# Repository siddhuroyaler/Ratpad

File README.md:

# Ratpad
It is my Hack club's project Hackpad 

I named my Hackpad Ratpad( i dont know why name it that just poped in my mind) 

# Challenges:-

It is my 1 st Hackclub projet , it was hard and confusing most of the confusion is in firmware and most of the time consuming was 3D model as it was my 1 my time makeing a 3D model 

# Specifications:-

 BOM:

5x Cherry MX Switches

6x SK6812 MINI Leds

1x XIAO RP2040

1x EC11 Rotary encoders

1x 0.91 inch OLED displays 

5x Blank DSA Keycaps

4x M3x16 Bolt

4x M3 Heatset

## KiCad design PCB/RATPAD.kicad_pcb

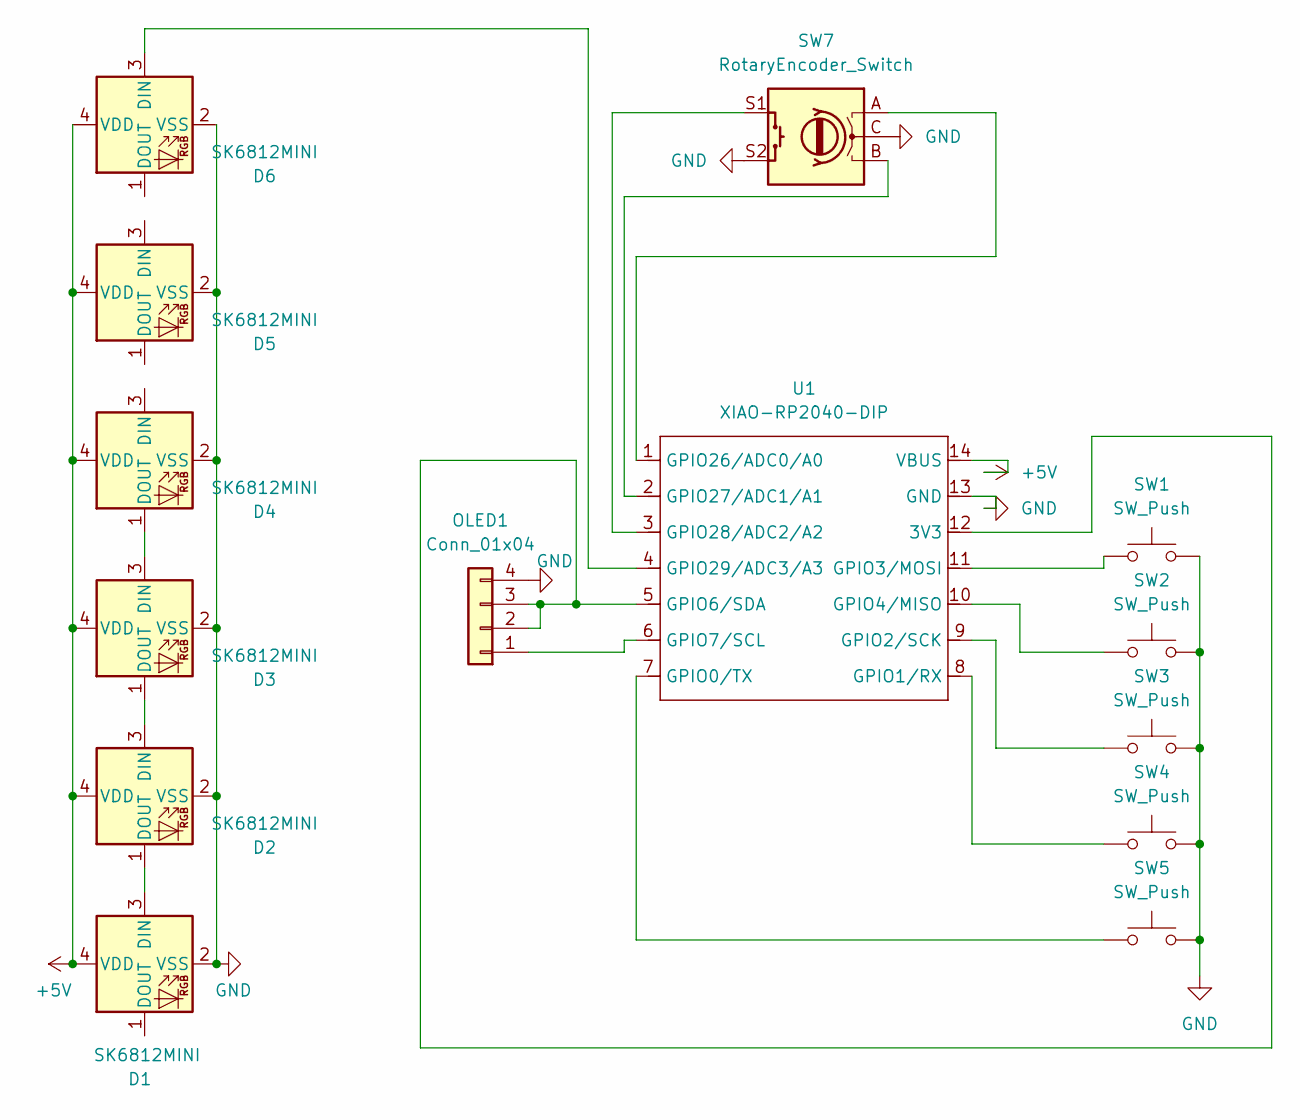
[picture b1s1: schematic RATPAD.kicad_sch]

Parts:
D1, D2, D3, D4, D5, D6: SK6812MINI; MX_SK6812MINI-E_REV
OLED1: Conn_01x04; SSD1306-0.91-OLED-4pin-128x32
SW1, SW2, SW3, SW4, SW5: SW_Push; SW_Cherry_MX_1.00u_PCB
SW7: RotaryEncoder_Switch; RotaryEncoder_Alps_EC11E-Switch_Vertical_H20mm_CircularMoun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
U1: XIAO-RP2040-DIP; XIAO-ESP32S3-DIP

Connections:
+5V: D1.4 (VDD), D2.4 (VDD), D3.4 (VDD), D4.4 (VDD), D5.4 (VDD), D6.4 (VDD), U1.14 (VBUS)
GND: D1.2 (VSS), D2.2 (VSS), D3.2 (VSS), D4.2 (VSS), D5.2 (VSS), D6.2 (VSS), OLED1.4, SW1.1, SW2.1, SW3.1, SW4.1, SW5.1, SW7.C, SW7.S2, U1.13 (GND)
unnamed: D1.3 (DIN), D2.1 (DOUT)
unnamed: D2.3 (DIN), D3.1 (DOUT)
unnamed: D3.3 (DIN), D4.1 (DOUT)
unnamed: D6.3 (DIN), U1.4 (GPIO29/ADC3/A3)
unnamed: OLED1.1, U1.6 (GPIO7/SCL)
unnamed: OLED1.2, OLED1.3, U1.5 (GPIO6/SDA), U1.12 (3V3)
unnamed: SW5.2, U1.7 (GPIO0/TX)
unnamed: SW4.2, U1.8 (GPIO1/RX)
unnamed: SW3.2, U1.9 (GPIO2/SCK)
unnamed: SW1.2, U1.11 (GPIO3/MOSI)
unnamed: SW2.2, U1.10 (GPIO4/MISO)
unnamed: SW7.A, U1.1 (GPIO26/ADC0/A0)
unnamed: SW7.B, U1.2 (GPIO27/ADC1/A1)
unnamed: SW7.S1, U1.3 (GPIO28/ADC2/A2)

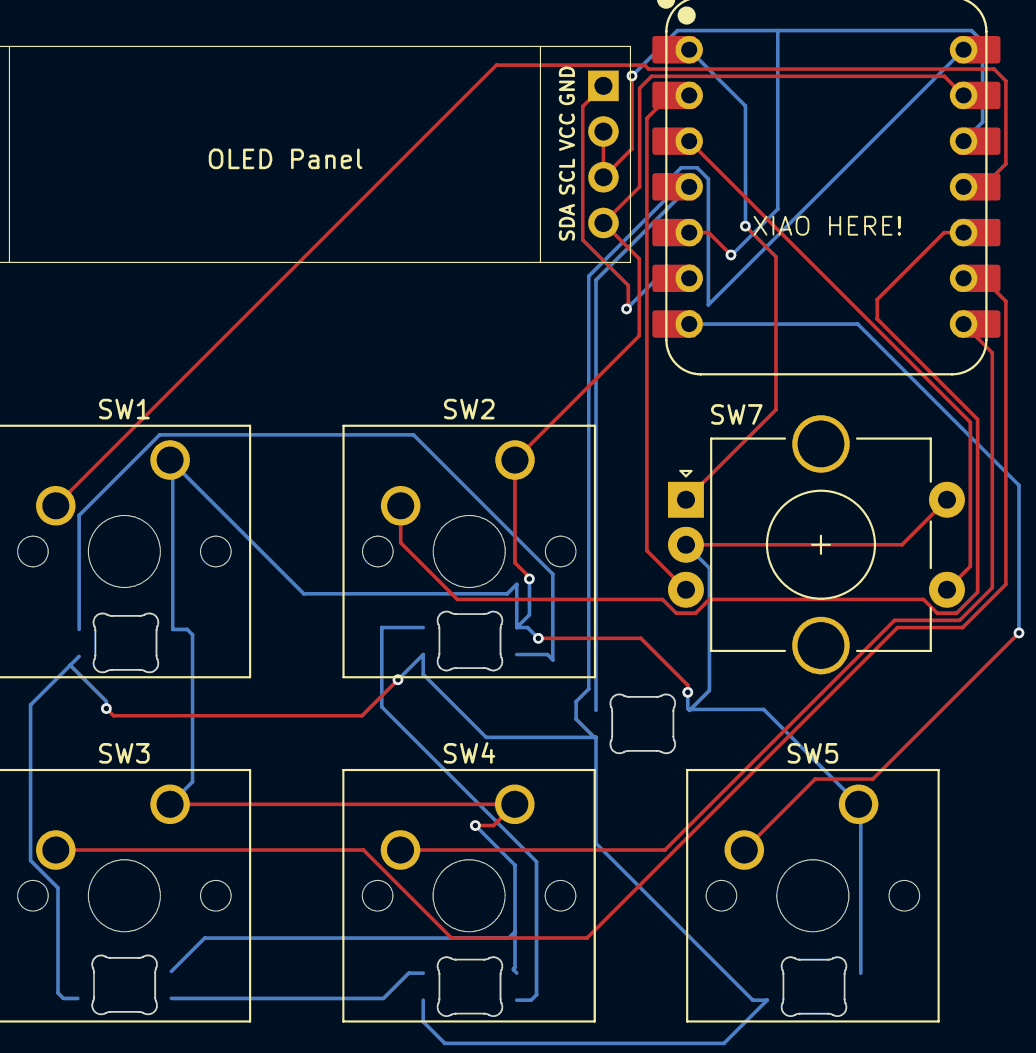
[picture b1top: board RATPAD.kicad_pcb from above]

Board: 2 copper layers, 14 parts (0 on the bottom side), 16 nets.
